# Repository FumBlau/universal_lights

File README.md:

# universal_lights
PCB and firmware for RGB and single color control based on attiny88

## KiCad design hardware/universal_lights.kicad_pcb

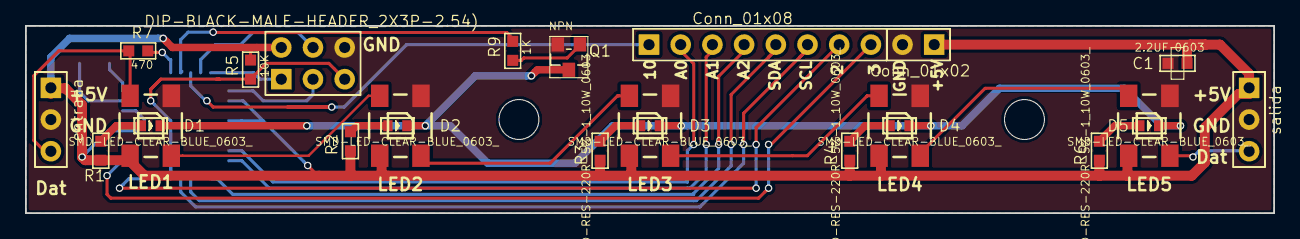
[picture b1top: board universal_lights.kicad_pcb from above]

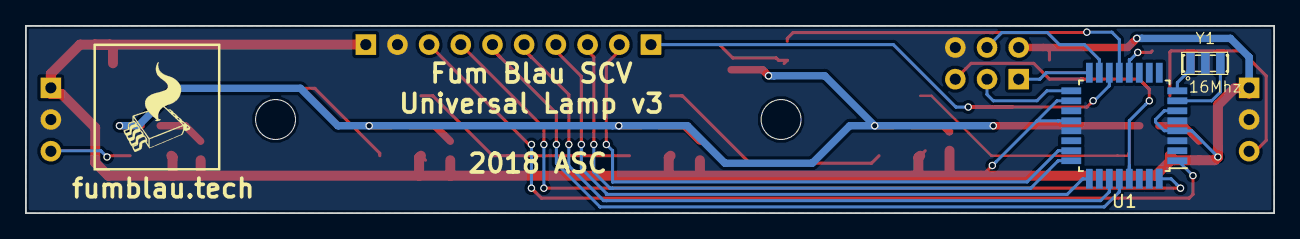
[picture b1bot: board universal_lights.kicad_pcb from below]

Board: 2 copper layers, 100.0 x 15.0 mm, 27 parts (2 on the bottom side), 31 nets.

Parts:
C1: 2.2UF 0603; C0603
D1, D2, D3, D4, D5: SMD-LED-CLEAR-BLUE_0603_; LED-0603
J1: entrada; H3-2.54
J2: salida; H3-2.54
J3: DIP-BLACK-MALE-HEADER_2X3P-2.54); H2X3-2.54
J4: Conn_01x08; H8-2.54
J5: Conn_01x02; H2-2.54
LED1, LED2, LED3, LED4, LED5: WS2812B
Q1: NPN; SOT-23
R1, R2, R3, R4, R6: SMD-RES-220R-5%-1_10W_0603_; R0603
R5: 10K; R0603
R7: 470; R0603
R9: 1K; R0603
U1: ATmega328P-AU; TQFP-32_7x7mm_Pitch0.8mm
Y1: 16Mhz; X3-SMD-3.6X1.3X0.8MM

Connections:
+5V: C1.1, J1.1, J2.1, J3.6, J5.1, LED1.1, LED2.1, LED3.1, LED4.1, LED5.1, R1.1, R2.1, R3.1, R4.1, R5.1, R6.1, U1.4, U1.6, U1.18, U1.20
/a0: J4.2, U1.23
/a1: J4.3, U1.24
/a2: J4.4, U1.25
/clk: J3.2, U1.17
/datos_led_in: J1.3, LED1.4, R7.2
/datos_led_out: J2.3, LED5.2
/int0: J4.7, U1.32
/int1: J4.8, U1.1
/miso: J3.1, U1.16
/mosi: J3.5, U1.15
/pwm1: R9.1, U1.13
/pwm2: J4.1, U1.14
/reset: J3.3, R5.2, U1.29
/scl: J4.6, U1.28
/sda: J4.5, U1.27
GND: C1.2, J1.2, J2.2, J3.4, J5.2, LED1.3, LED2.3, LED3.3, LED4.3, LED5.3, Q1.2, U1.3, U1.5, U1.21, Y1.2
unnamed: D1.+, R1.2
unnamed: D1.-, D2.-, D3.-, D4.-, D5.-, Q1.3
unnamed: D2.+, R2.2
unnamed: D3.+, R3.2
unnamed: D4.+, R4.2
unnamed: D5.+, R6.2
unnamed: LED1.2, LED2.4
unnamed: LED2.2, LED3.4
unnamed: LED3.2, LED4.4
unnamed: LED4.2, LED5.4
unnamed: Q1.1, R9.2
unnamed: R7.1, U1.12
unnamed: U1.7, Y1.3
unnamed: U1.8, Y1.1

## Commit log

2017-09-14 V2 hardware, V0 firmware
2018-05-29 WIP del atmega 328 para ADCtouch
2018-05-29 instalado atmega 328, ajustados agujeros de montaje, cambio silk versión
2018-05-29 añado 470R a entrada datos led, muevo cristal para que sea mas facil de soldar
2018-05-29 añado otra huella de condensador, gerbers nuevos
